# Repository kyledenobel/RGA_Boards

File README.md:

# RGA_Boards
PCB Board design and development for RGA (Recording Guitar Amplifier)

## Issues and Organization
After completing an issue for board design, please mark as resolved and mention your branch/merge and create another issue for fabrication with the milestone "All Boards Have Been Fabricated" linked to the issue.
Similarly, after fabrication is finished, make an issue for testing with the milestone "All Boards Have Been Tested" linked to the issue.

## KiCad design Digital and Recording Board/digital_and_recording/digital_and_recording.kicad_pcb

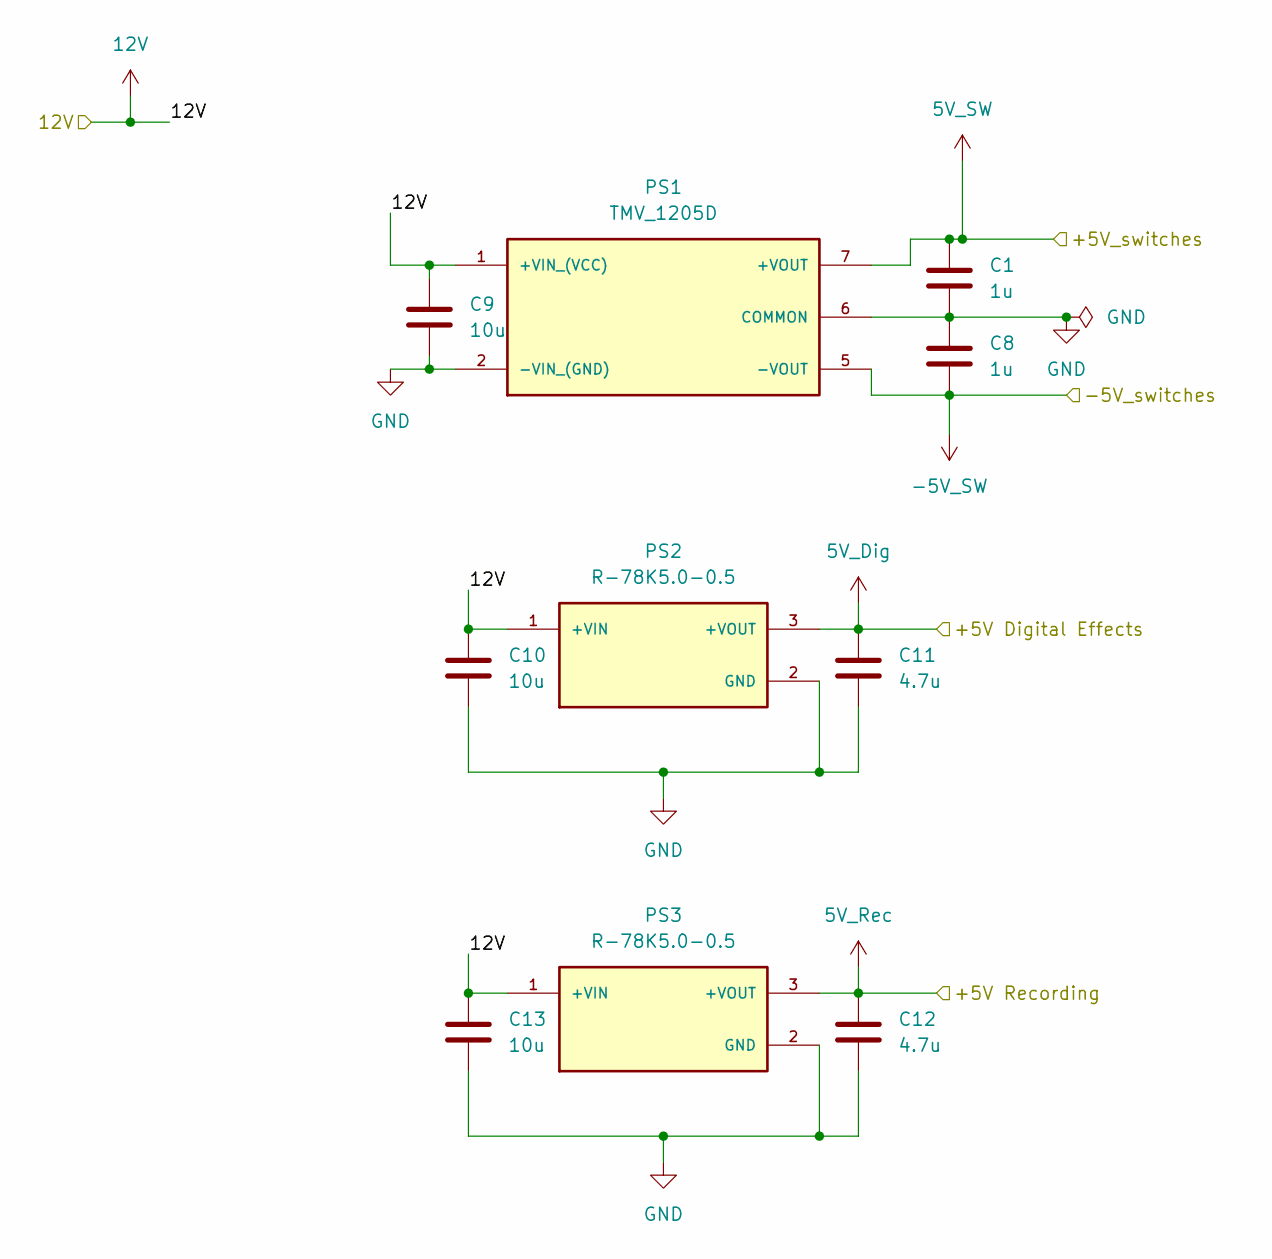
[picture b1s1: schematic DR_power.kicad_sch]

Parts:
C1, C8: 1u; C_0603_1608Metric
C9, C10, C13: 10u; C_0603_1608Metric
C11, C12: 4.7u; C_0603_1608Metric
PS1: TMV_1205D; CONV_TMV_1205D; PARTREV March 26, 2020; DigiKey_Part_Number 1951-2505-ND
PS2, PS3: R-78K5.0-0.5; CONV_R-78K5.0-0.5; PARTREV 0/2023; DigiKey_Part_Number 945-R-78K5.0-0.5-ND

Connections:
5V_Dig: C11.1, PS2.3 (+VOUT); also elsewhere on the board
5V_Rec: C12.1, PS3.3 (+VOUT); also elsewhere on the board
5V_SW: C1.1, PS1.7 (+VOUT); also elsewhere on the board
12V: C9.1, C10.1, C13.1, PS1.1 (+VIN_(VCC)), PS2.1 (+VIN), PS3.1 (+VIN); also elsewhere on the board
-5V_SW: C8.2, PS1.5 (-VOUT); also elsewhere on the board
GND: C1.2, C8.1, C9.2, C10.2, C11.2, C12.2, C13.2, PS1.2 (-VIN_(GND)), PS1.6 (COMMON), PS2.2 (GND), PS3.2 (GND); also elsewhere on the board

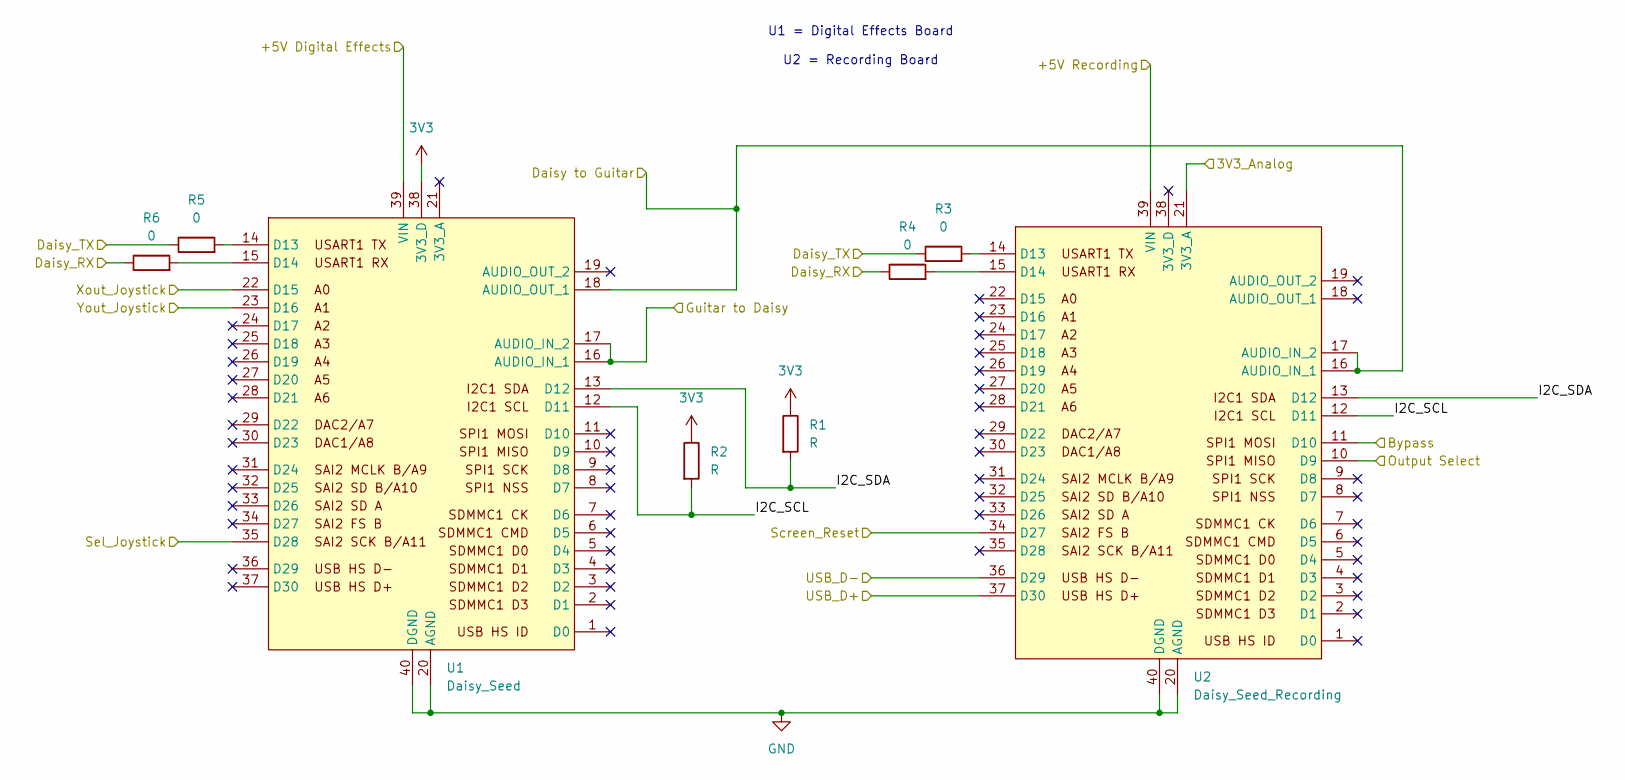
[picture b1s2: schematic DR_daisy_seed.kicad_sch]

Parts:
R1, R2: R; R_0603_1608Metric
R3, R4, R5, R6: 0; R_0603_1608Metric
U1: Daisy_Seed; DAISY_SEED
U2: Daisy_Seed_Recording; DAISY_SEED

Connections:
3V3: R1.1, R2.1, U1.38 (3V3_D)
5V_Dig: U1.39 (VIN); also elsewhere on the board
5V_Rec: U2.39 (VIN); also elsewhere on the board
/Connectors/3V3_Analog: U2.21 (3V3_A); also elsewhere on the board
/Connectors/Bypass: U2.11 (D10); also elsewhere on the board
/Connectors/Daisy to Guitar: U1.18 (AUDIO_OUT_1), U2.16 (AUDIO_IN_1), U2.17 (AUDIO_IN_2); also elsewhere on the board
/Connectors/Daisy_RX: R4.1, R6.1; also elsewhere on the board
/Connectors/Daisy_TX: R3.1, R5.1; also elsewhere on the board
/Connectors/Guitar to Daisy: U1.16 (AUDIO_IN_1), U1.17 (AUDIO_IN_2); also elsewhere on the board
/Connectors/Output Select: U2.10 (D9); also elsewhere on the board
/Connectors/Screen_Reset: U2.34 (D27); also elsewhere on the board
/Connectors/Sel_Joystick: U1.35 (D28); also elsewhere on the board
/Connectors/USB_D+: U2.37 (D30); also elsewhere on the board
/Connectors/USB_D-: U2.36 (D29); also elsewhere on the board
/Connectors/Xout_Joystick: U1.22 (D15); also elsewhere on the board
/Connectors/Yout_Joystick: U1.23 (D16); also elsewhere on the board
/Daisy Seed/I2C_SCL: R2.2, U1.12 (D11), U2.12 (D11)
/Daisy Seed/I2C_SDA: R1.2, U1.13 (D12), U2.13 (D12)
GND: U1.20 (AGND), U1.40 (DGND), U2.20 (AGND), U2.40 (DGND); also elsewhere on the board
unnamed: R5.2, U1.14 (D13)
unnamed: R6.2, U1.15 (D14)
unnamed: R3.2, U2.14 (D13)
unnamed: R4.2, U2.15 (D14)

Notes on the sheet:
U1 = Digital Effects Board U2 = Recording Board

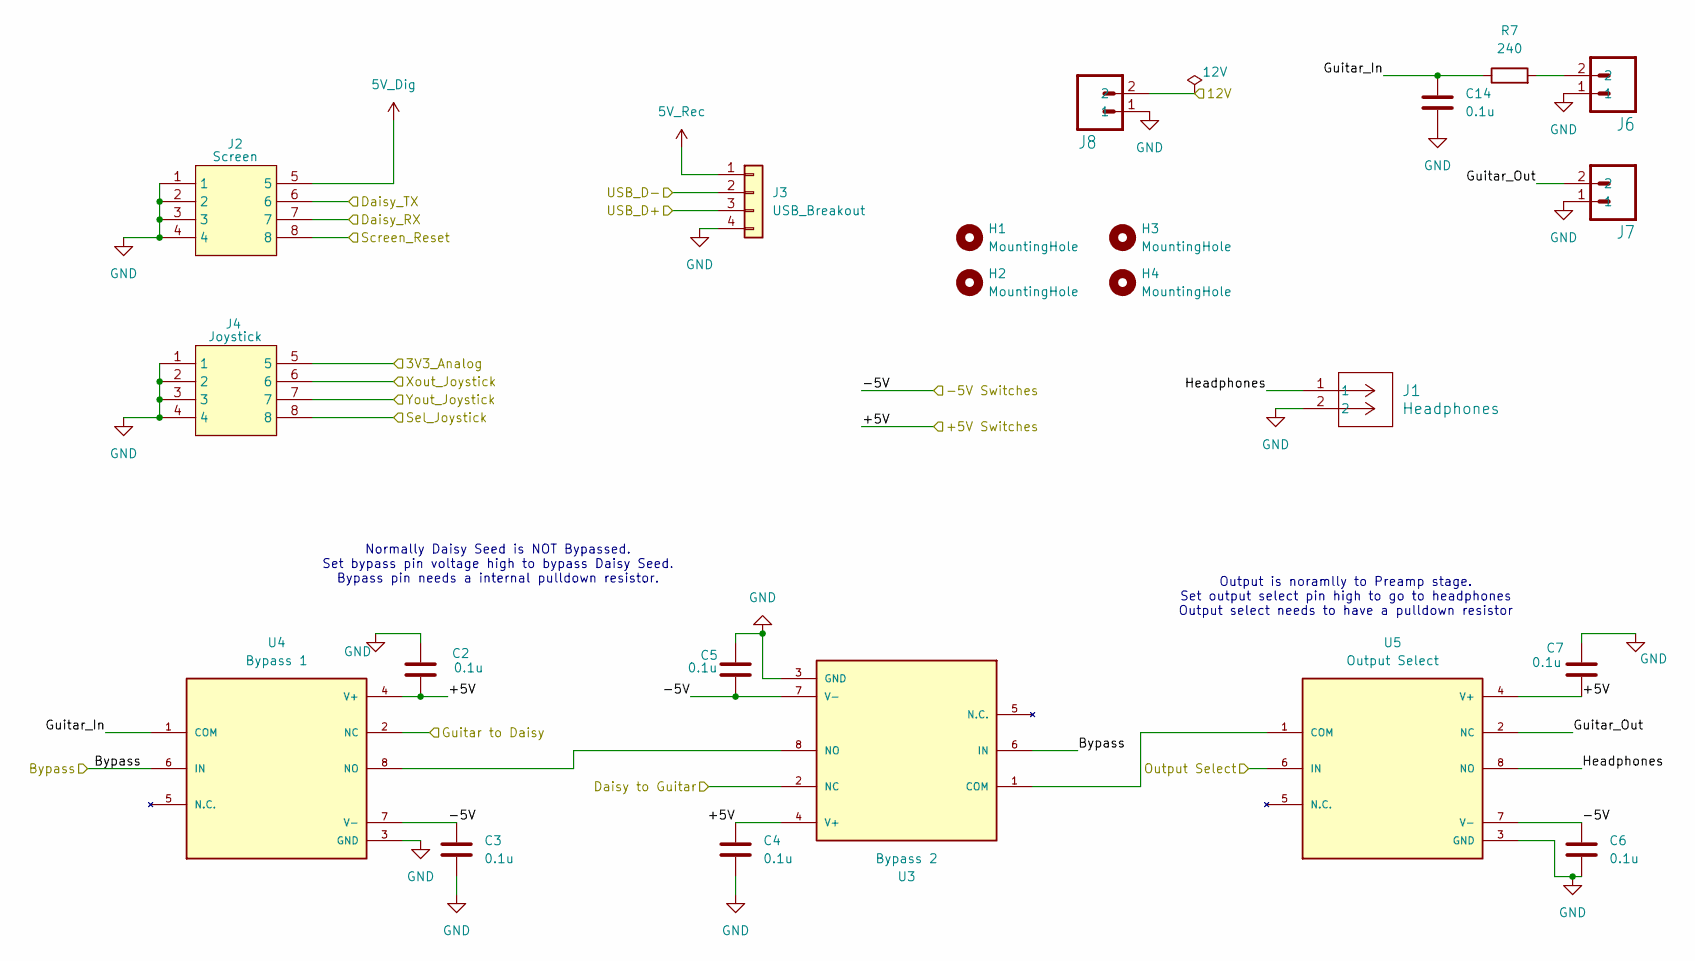
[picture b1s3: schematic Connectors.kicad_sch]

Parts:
C2, C3, C4, C5, C6, C7, C14: 0.1u; C_0603_1608Metric
H1, H2, H3, H4: MountingHole; MountingHole_2.7mm_M2.5
J1: Headphones; CONN_SD-5566-002_02_MOL
J2: Screen; MOLEX_2068320801
J3: USB_Breakout; PinHeader_1x04_P2.54mm_Vertical
J4: Joystick; MOLEX_2068320801
J6, J7: MINIFIT-2-VERT; Molex_Mini-Fit_Jr_5566-02A_2x01_P4.20mm_Vertical
J8: MINIFIT-2-VERT; Molex_Mega-Fit_76829-0102_2x01_P5.70mm_Vertical
R7: 240; R_0603_1608Metric
U3: Bypass 2; SOT65P280X145-8N; PARTREV E; DigiKey_Part_Number 296-27523-1-ND
U4: Bypass 1; SOT65P280X145-8N; PARTREV E; DigiKey_Part_Number 296-27523-1-ND
U5: Output Select; SOT65P280X145-8N; PARTREV E; DigiKey_Part_Number 296-27523-1-ND

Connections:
5V_Dig: J2.5; also elsewhere on the board
5V_Rec: J3.1; also elsewhere on the board
5V_SW: C2.2, C4.1, C7.2, U3.4 (V+), U4.4 (V+), U5.4 (V+); also elsewhere on the board
12V: J8.2; also elsewhere on the board
-5V_SW: C3.1, C5.2, C6.1, U3.7 (V-), U4.7 (V-), U5.7 (V-); also elsewhere on the board
/Connectors/3V3_Analog: J4.5; also elsewhere on the board
/Connectors/Bypass: U3.6 (IN), U4.6 (IN); also elsewhere on the board
/Connectors/Daisy to Guitar: U3.2 (NC); also elsewhere on the board
/Connectors/Daisy_RX: J2.7; also elsewhere on the board
/Connectors/Daisy_TX: J2.6; also elsewhere on the board
/Connectors/Guitar to Daisy: U4.2 (NC); also elsewhere on the board
/Connectors/Guitar_In: C14.1, R7.1, U4.1 (COM)
/Connectors/Guitar_Out: J7.2, U5.2 (NC)
/Connectors/Headphones: J1.1, U5.8 (NO)
/Connectors/Output Select: U5.6 (IN); also elsewhere on the board
/Connectors/Screen_Reset: J2.8; also elsewhere on the board
/Connectors/Sel_Joystick: J4.8; also elsewhere on the board
/Connectors/USB_D+: J3.3; also elsewhere on the board
/Connectors/USB_D-: J3.2; also elsewhere on the board
/Connectors/Xout_Joystick: J4.6; also elsewhere on the board
/Connectors/Yout_Joystick: J4.7; also elsewhere on the board
GND: C2.1, C3.2, C4.2, C5.1, C6.2, C7.1, C14.2, J1.2, J2.1, J2.2, J2.3, J2.4, J3.4, J4.1, J4.2, J4.3, J4.4, J6.1, J7.1, J8.1, U3.3 (GND), U4.3 (GND), U5.3 (GND); also elsewhere on the board
unnamed: J6.2, R7.2
unnamed: U3.1 (COM), U5.1 (COM)
unnamed: U3.8 (NO), U4.8 (NO)

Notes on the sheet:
Normally Daisy Seed is NOT Bypassed. Set bypass pin voltage high to bypass Daisy Seed. Bypass pin needs a internal pulldown resistor.
Output is noramlly to Preamp stage. Set output select pin high to go to headphones Output select needs to have a pulldown resistor

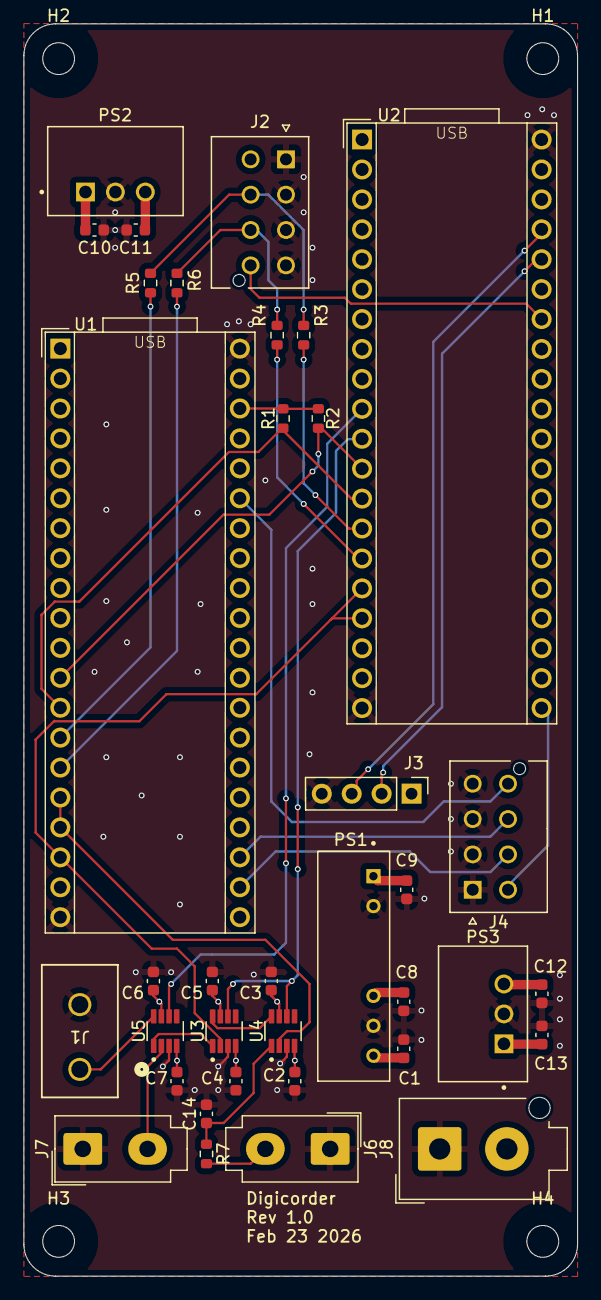
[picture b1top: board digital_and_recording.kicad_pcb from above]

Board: 4 copper layers, 47.0 x 106.3 mm, 40 parts (0 on the bottom side), 32 nets.

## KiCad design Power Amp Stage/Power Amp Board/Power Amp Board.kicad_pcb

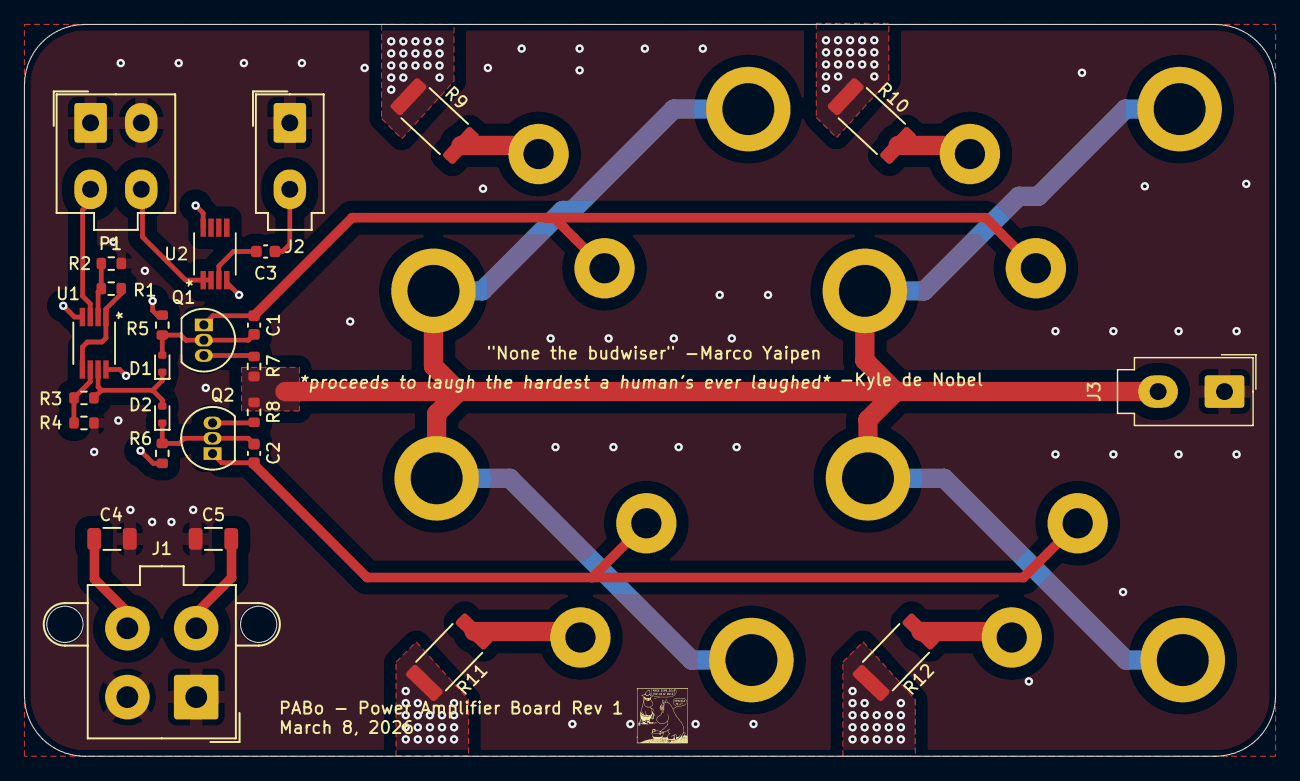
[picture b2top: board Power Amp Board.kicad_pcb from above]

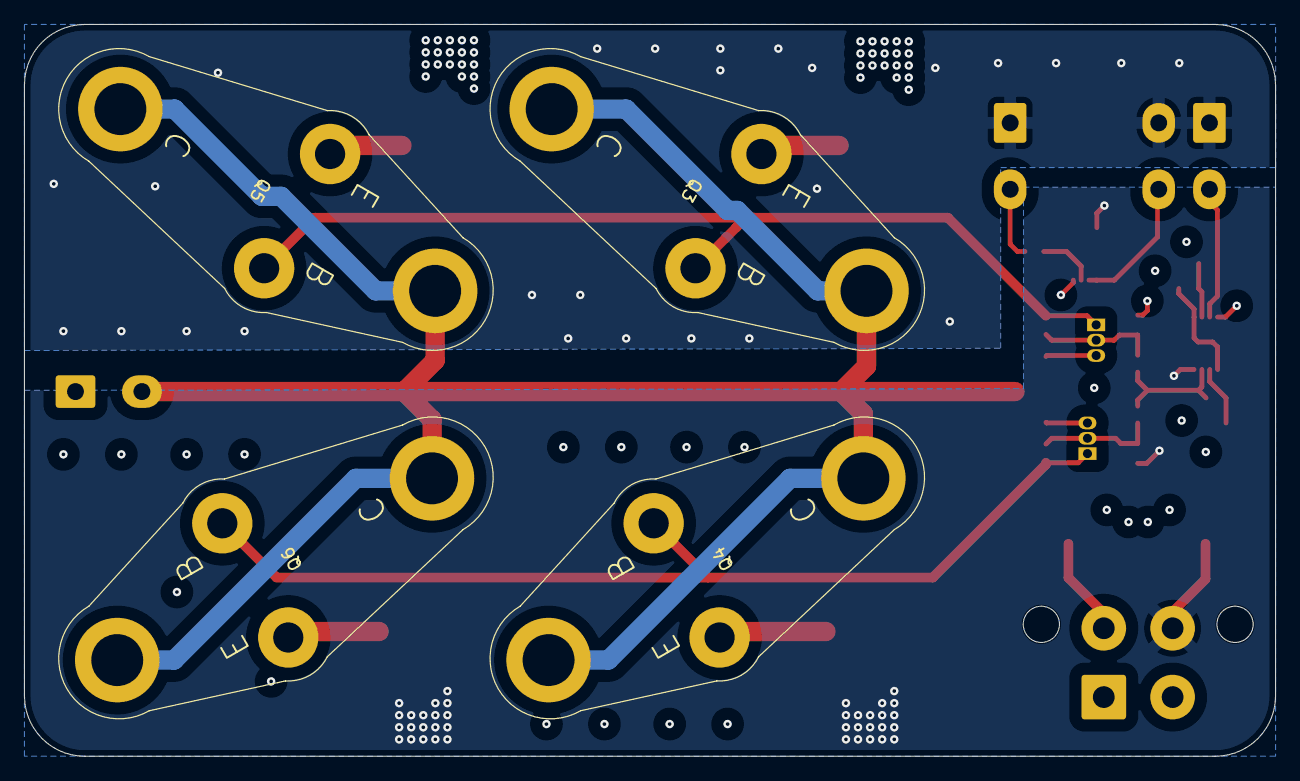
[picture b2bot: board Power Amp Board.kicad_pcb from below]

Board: 4 copper layers, 103.6 x 60.6 mm, 31 parts (4 on the bottom side), 22 nets.

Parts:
C1, C2: C; C_0603_1608Metric
C3: 0.1u; C_0603_1608Metric
C4, C5: 100u; C_1206_3216Metric
D1, D2: 1N4148WT; D_SOD-523
J1: Molex_Mega-Fit_76829-0004_2x02_P5.70mm_Vertical
J2, J3: Conn_01x02; Molex_Mini-Fit_Jr_5566-02A_2x01_P4.20mm_Vertical
P1: Molex_Mini-Fit_Jr_5566-04A_2x02_P4.20mm_Vertical
Q1: BC549; TO-92_Inline
Q2: BC559; TO-92_Inline
Q3, Q5: MJ15004; MJ15000
Q4, Q6: MJ15003; MJ15000
R1, R3: 100k; R_0603_1608Metric
R2, R4, R5, R6: 10k; R_0603_1608Metric
R7, R8: 100; R_0603_1608Metric
R9, R10, R11, R12: 4.7; R_2512_6332Metric
U1, U2: ADA4522-2ARMZ-R7; RM-8_ADI

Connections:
24V: C5.1, J1.3, R5.1, R9.1, R10.1, U1.4 (V-), U2.4 (V-)
-24V: C4.1, J1.4, R6.2, R11.2, R12.2, U1.8 (V+), U2.8 (V+)
/audio_in+: C3.1, J2.2
/audio_out+: J3.2, Q3.3 (C), Q4.3 (C), Q5.3 (C), Q6.3 (C), R7.2, R8.1
/buffer: P1.4 (H), U2.1 (OUTA), U2.2 (INA-)
/out1: R1.1, U1.1 (OUTA), U1.5 (INB+)
/out2: D1.1 (K), D2.2 (A), R3.1, U1.7 (OUTB)
/post_pot: P1.3 (W), U1.3 (INA+)
GND: C4.2, C5.2, J1.1, J1.2, J2.1, J3.1, P1.1 (GND), P1.2 (L), R2.1, R4.1
unnamed: C1.2, D1.2 (A), Q1.2 (B), R5.2
unnamed: C2.1, D2.1 (K), Q2.2 (B), R6.1
unnamed: C1.1, Q1.1 (C), Q3.2 (B), Q5.2 (B)
unnamed: Q1.3 (E), R7.1
unnamed: C2.2, Q2.1 (C), Q4.2 (B), Q6.2 (B)
unnamed: Q2.3 (E), R8.2
unnamed: Q3.1 (E), R9.2
unnamed: Q4.1 (E), R11.1
unnamed: Q5.1 (E), R10.2
unnamed: Q6.1 (E), R12.1
unnamed: R1.2, R2.2, U1.2 (INA-)
unnamed: R3.2, R4.2, U1.6 (INB-)
unnamed: C3.2, U2.3 (INA+)

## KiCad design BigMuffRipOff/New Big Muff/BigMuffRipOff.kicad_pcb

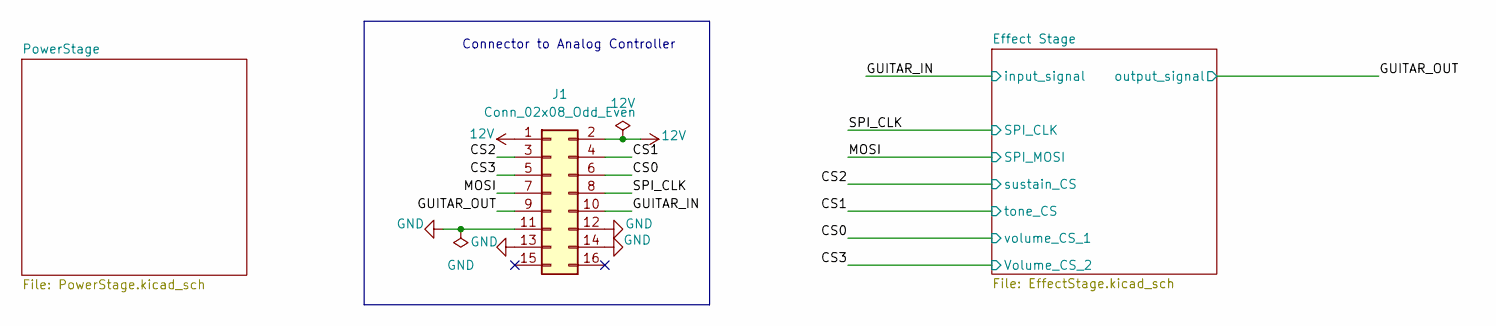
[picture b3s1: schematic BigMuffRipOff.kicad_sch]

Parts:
J1: Conn_02x08_Odd_Even; PinHeader_2x08_P2.54mm_Horizontal

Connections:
12V: J1.1, J1.2; also elsewhere on the board
/CS0: J1.6; also elsewhere on the board
/CS1: J1.4; also elsewhere on the board
/CS2: J1.3; also elsewhere on the board
/CS3: J1.5; also elsewhere on the board
/GUITAR_IN: J1.10; also elsewhere on the board
/GUITAR_OUT: J1.9; also elsewhere on the board
/MOSI: J1.7; also elsewhere on the board
/SPI_CLK: J1.8; also elsewhere on the board
GND: J1.11, J1.12, J1.13, J1.14; also elsewhere on the board

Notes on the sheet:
Connector to Analog Controller

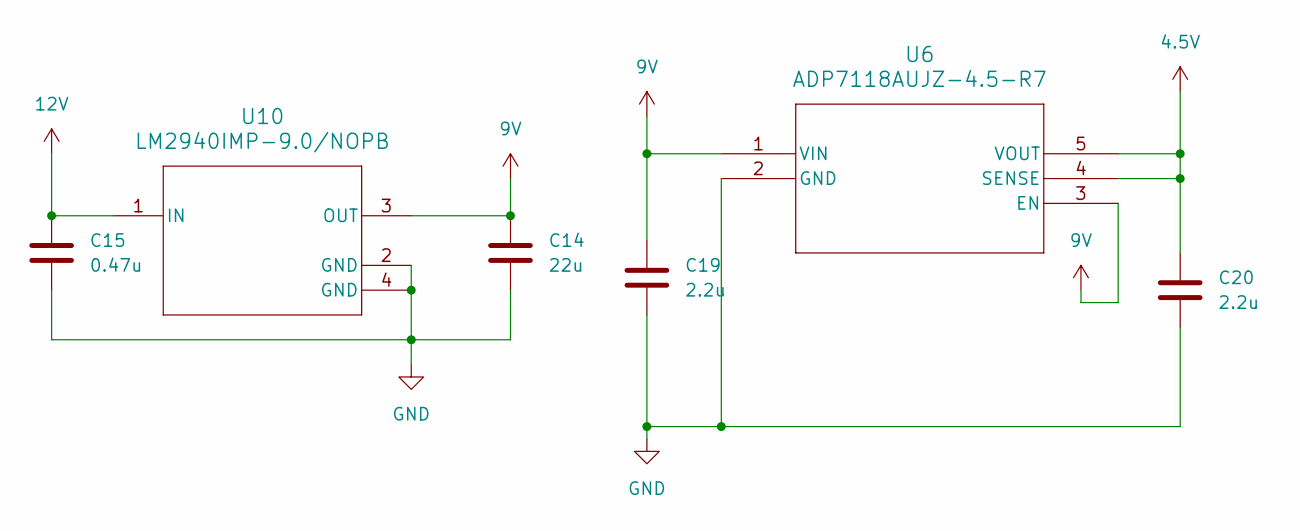
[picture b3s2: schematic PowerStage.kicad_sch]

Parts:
C14: 22u; C_0603_1608Metric
C15: 0.47u; C_0603_1608Metric
C19, C20: 2.2u; C_0603_1608Metric
U6: ADP7118AUJZ-4.5-R7; UJ-5_ADI
U10: LM2940IMP-9.0/NOPB; DCY0004A_N

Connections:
4.5V: C20.1, U6.4 (SENSE), U6.5 (VOUT); also elsewhere on the board
9V: C14.1, C19.1, U6.1 (VIN), U6.3 (EN), U10.3 (OUT); also elsewhere on the board
12V: C15.1, U10.1 (IN); also elsewhere on the board
GND: C14.2, C15.2, C19.2, C20.2, U6.2 (GND), U10.2 (GND), U10.4 (GND); also elsewhere on the board

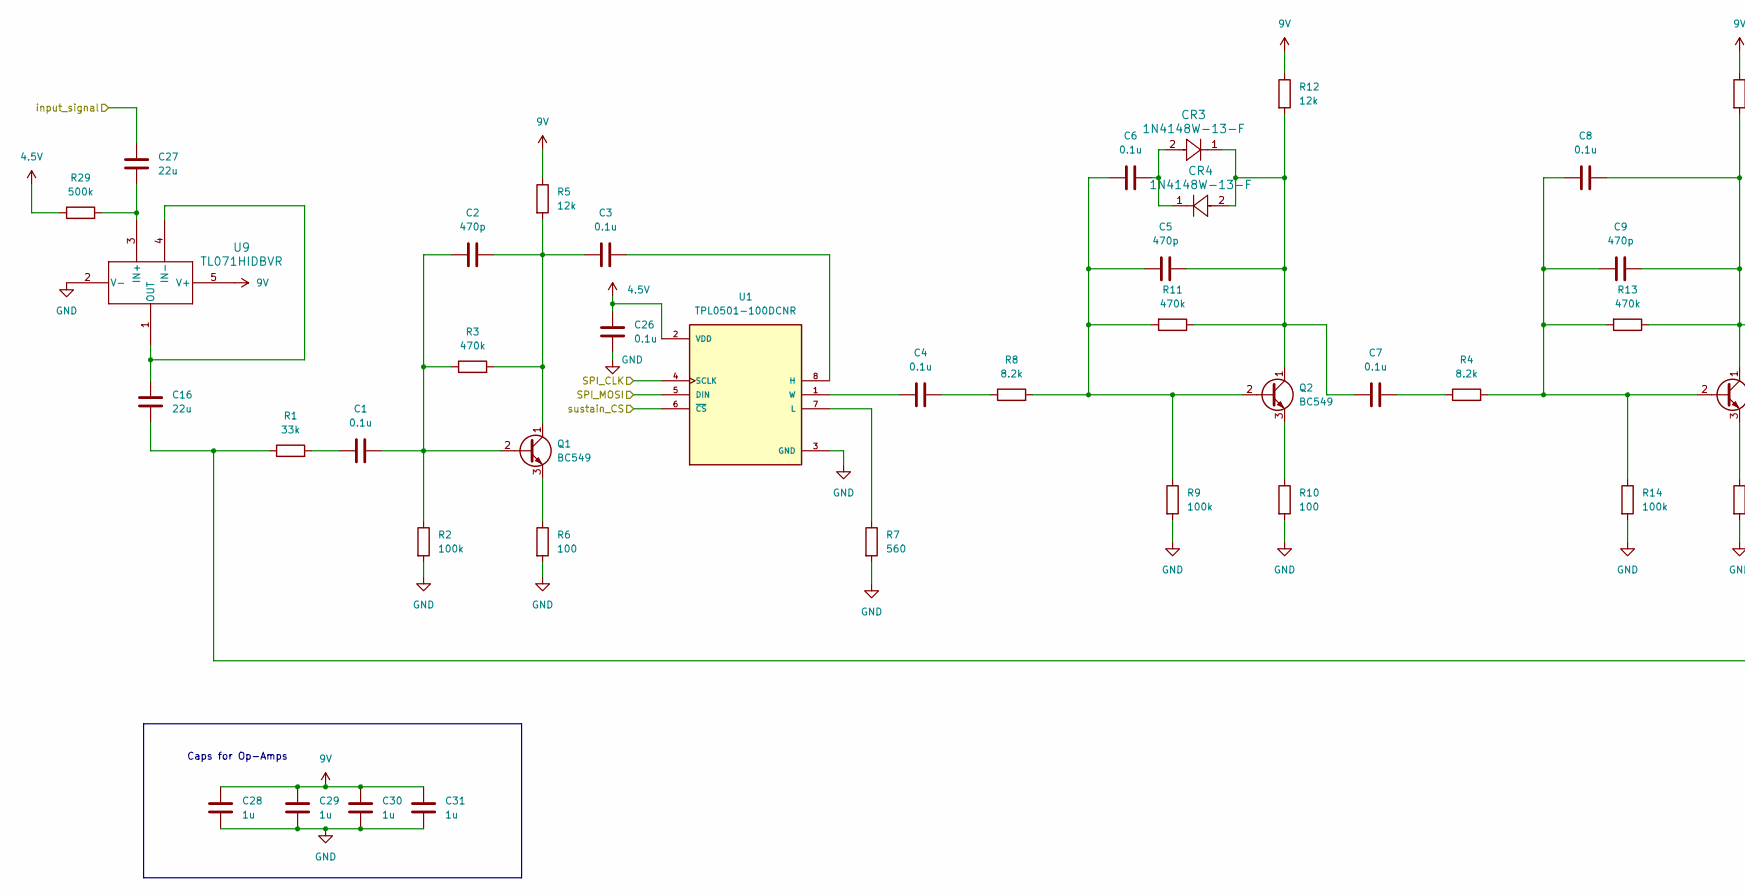
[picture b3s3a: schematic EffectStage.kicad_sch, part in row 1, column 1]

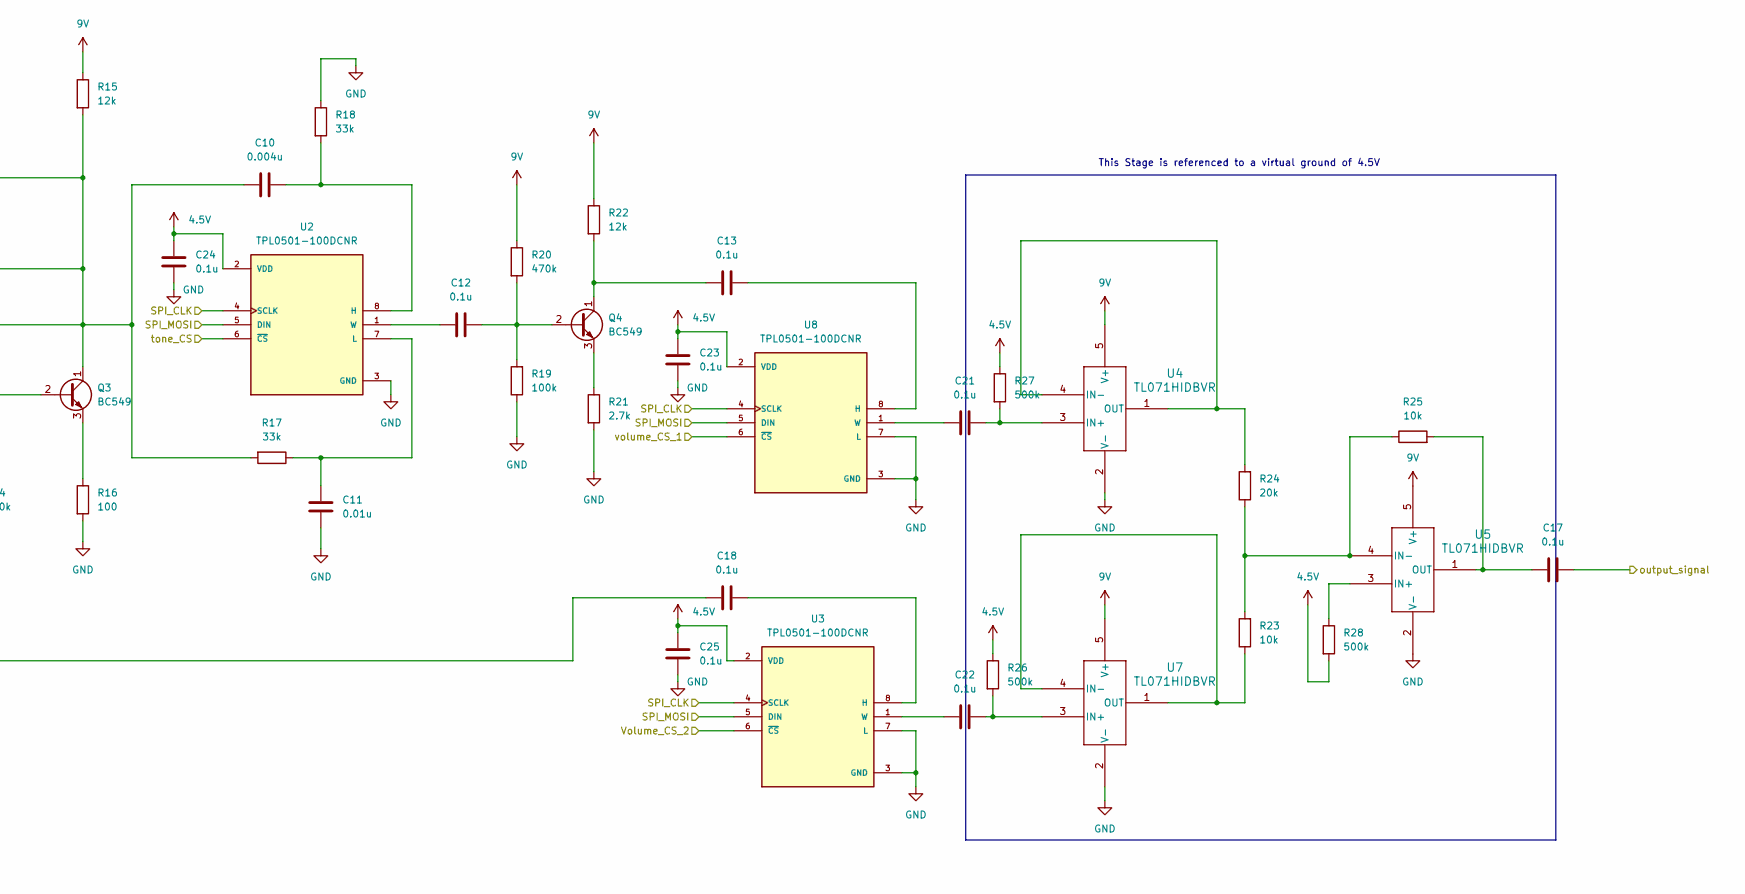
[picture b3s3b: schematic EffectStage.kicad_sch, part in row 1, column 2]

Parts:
C1, C3, C4, C6, C7, C8, C12, C13, C17, C18, C21, C22, C23, C24, C25, C26: 0.1u; C_0603_1608Metric
C2, C5, C9: 470p; C_0603_1608Metric
C10: 0.004u; C_0603_1608Metric
C11: 0.01u; C_0603_1608Metric
C16, C27: 22u; C_0603_1608Metric
C28, C29, C30, C31: 1u; C_0603_1608Metric
CR3, CR4: 1N4148W-13-F; SOD123_DIO
Q1, Q2, Q3, Q4: BC549; TO-92_Inline
R1, R17, R18: 33k; R_0603_1608Metric
R2, R9, R14, R19: 100k; R_0603_1608Metric
R3, R11, R13, R20: 470k; R_0603_1608Metric
R4, R8: 8.2k; R_0603_1608Metric
R5, R12, R15, R22: 12k; R_0603_1608Metric
R6, R10, R16: 100; R_0603_1608Metric
R7: 560; R_0603_1608Metric
R21: 2.7k; R_0603_1608Metric
R23, R25: 10k; R_0603_1608Metric
R24: 20k; R_0603_1608Metric
R26, R27, R28, R29: 500k; R_0603_1608Metric
U1, U2, U3, U8: TPL0501-100DCNR; SOT65P280X145-8N; PARTREV C
U4, U5, U7, U9: TL071HIDBVR; SOT23_DBV_5_TEX

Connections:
4.5V: C23.1, C24.1, C25.1, C26.1, R26.1, R27.1, R28.2, R29.1, U1.2 (VDD), U2.2 (VDD), U3.2 (VDD), U8.2 (VDD); also elsewhere on the board
9V: C28.1, C29.1, C30.1, C31.1, R5.1, R12.1, R15.1, R20.1, R22.1, U4.5 (V+), U5.5 (V+), U7.5 (V+), U9.5 (V+); also elsewhere on the board
/CS0: U8.6 (~CS); also elsewhere on the board
/CS1: U2.6 (~CS); also elsewhere on the board
/CS2: U1.6 (~CS); also elsewhere on the board
/CS3: U3.6 (~CS); also elsewhere on the board
/GUITAR_IN: C27.1; also elsewhere on the board
/GUITAR_OUT: C17.1; also elsewhere on the board
/MOSI: U1.5 (DIN), U2.5 (DIN), U3.5 (DIN), U8.5 (DIN); also elsewhere on the board
/SPI_CLK: U1.4 (SCLK), U2.4 (SCLK), U3.4 (SCLK), U8.4 (SCLK); also elsewhere on the board
GND: C11.2, C23.2, C24.2, C25.2, C26.2, C28.2, C29.2, C30.2, C31.2, R2.2, R6.2, R7.2, R9.2, R10.2, R14.2, R16.2, R18.1, R19.1, R21.2, U1.3 (GND), U2.3 (GND), U3.3 (GND), U3.7 (L), U4.2 (V-), U5.2 (V-), U7.2 (V-), U8.3 (GND), U8.7 (L), U9.2 (V-); also elsewhere on the board
unnamed: C1.2, R1.2
unnamed: C4.1, R8.1
unnamed: C6.1, CR3.2, CR4.1
unnamed: C7.1, R4.1
unnamed: C16.2, C18.2, R1.1
unnamed: C1.1, C2.2, Q1.2 (B), R2.1, R3.1
unnamed: C2.1, C3.2, Q1.1 (C), R3.2, R5.2
unnamed: Q1.3 (E), R6.1
unnamed: C5.2, C6.2, Q2.2 (B), R8.2, R9.1, R11.2
unnamed: C5.1, C7.2, CR3.1, CR4.2, Q2.1 (C), R11.1, R12.2
unnamed: Q2.3 (E), R10.1
unnamed: C8.2, C9.2, Q3.2 (B), R4.2, R13.2, R14.1
unnamed: C8.1, C9.1, C10.2, Q3.1 (C), R13.1, R15.2, R17.2
unnamed: Q3.3 (E), R16.1
unnamed: C12.1, Q4.2 (B), R19.2, R20.2
unnamed: C13.2, Q4.1 (C), R22.2
unnamed: Q4.3 (E), R21.1
unnamed: C3.1, U1.8 (H)
unnamed: R7.1, U1.7 (L)
unnamed: C4.2, U1.1 (W)
unnamed: C10.1, R18.2, U2.8 (H)
unnamed: C11.1, R17.1, U2.7 (L)
unnamed: C12.2, U2.1 (W)
unnamed: C18.1, U3.8 (H)
unnamed: C22.1, U3.1 (W)
unnamed: C21.2, R27.2, U4.3 (IN+)
unnamed: R24.2, U4.1 (OUT), U4.4 (IN-)
unnamed: R28.1, U5.3 (IN+)
unnamed: R23.2, R24.1, R25.1, U5.4 (IN-)
unnamed: C17.2, R25.2, U5.1 (OUT)
unnamed: C22.2, R26.2, U7.3 (IN+)
unnamed: R23.1, U7.1 (OUT), U7.4 (IN-)
unnamed: C13.1, U8.8 (H)
unnamed: C21.1, U8.1 (W)
unnamed: C27.2, R29.2, U9.3 (IN+)
unnamed: C16.1, U9.1 (OUT), U9.4 (IN-)

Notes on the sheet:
This Stage is referenced to a virtual ground of 4.5V
Caps for Op-Amps

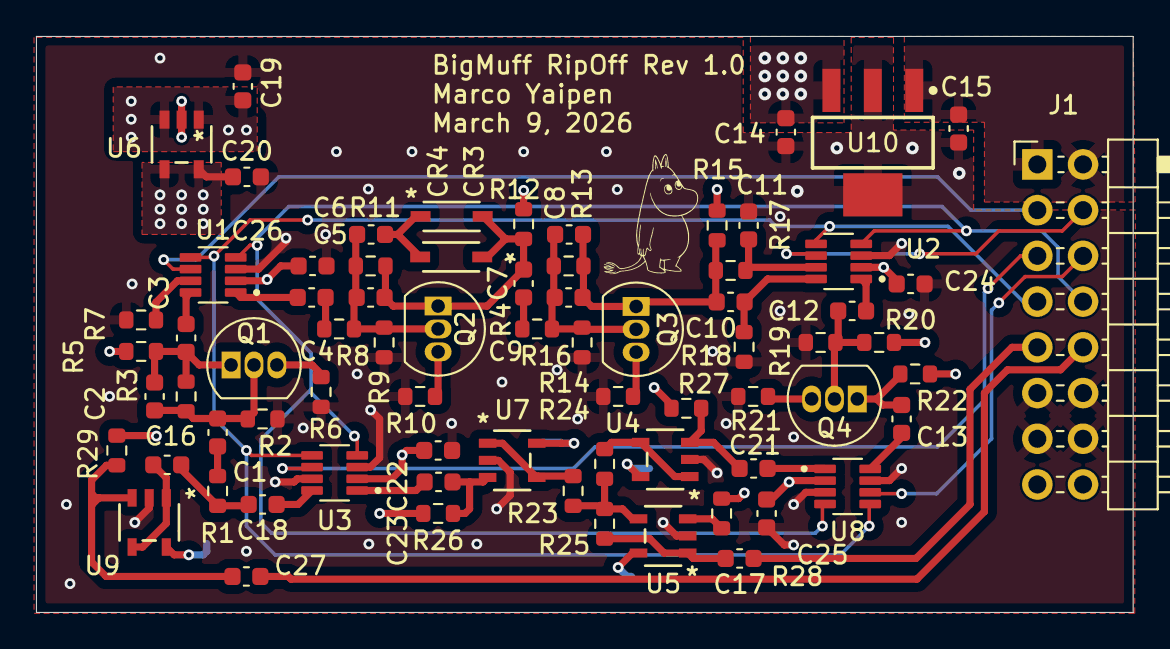
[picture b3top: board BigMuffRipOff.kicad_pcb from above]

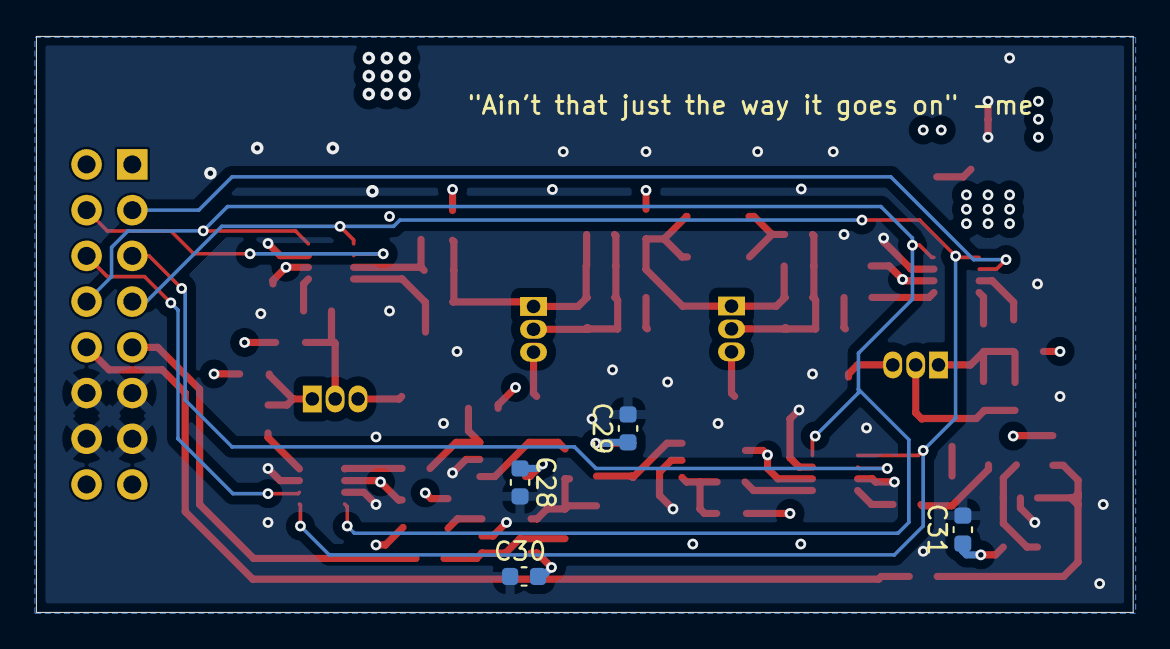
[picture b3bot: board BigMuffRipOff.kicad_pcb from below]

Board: 4 copper layers, 60.9 x 32.0 mm, 77 parts (4 on the bottom side), 48 nets.
